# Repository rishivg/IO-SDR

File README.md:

# IO-SDR_Rev_1.1
 
IO-SDR is an open-source software-defined FPGA radio hardware platform that serves as a successor to the Pluto SDR Learning Module. Support includes and is not limited to:

- dual multichannel transmission and reception
- Gigabit Ethernet connection
- Embedded Linux SoC development
- GNU Radio blocks

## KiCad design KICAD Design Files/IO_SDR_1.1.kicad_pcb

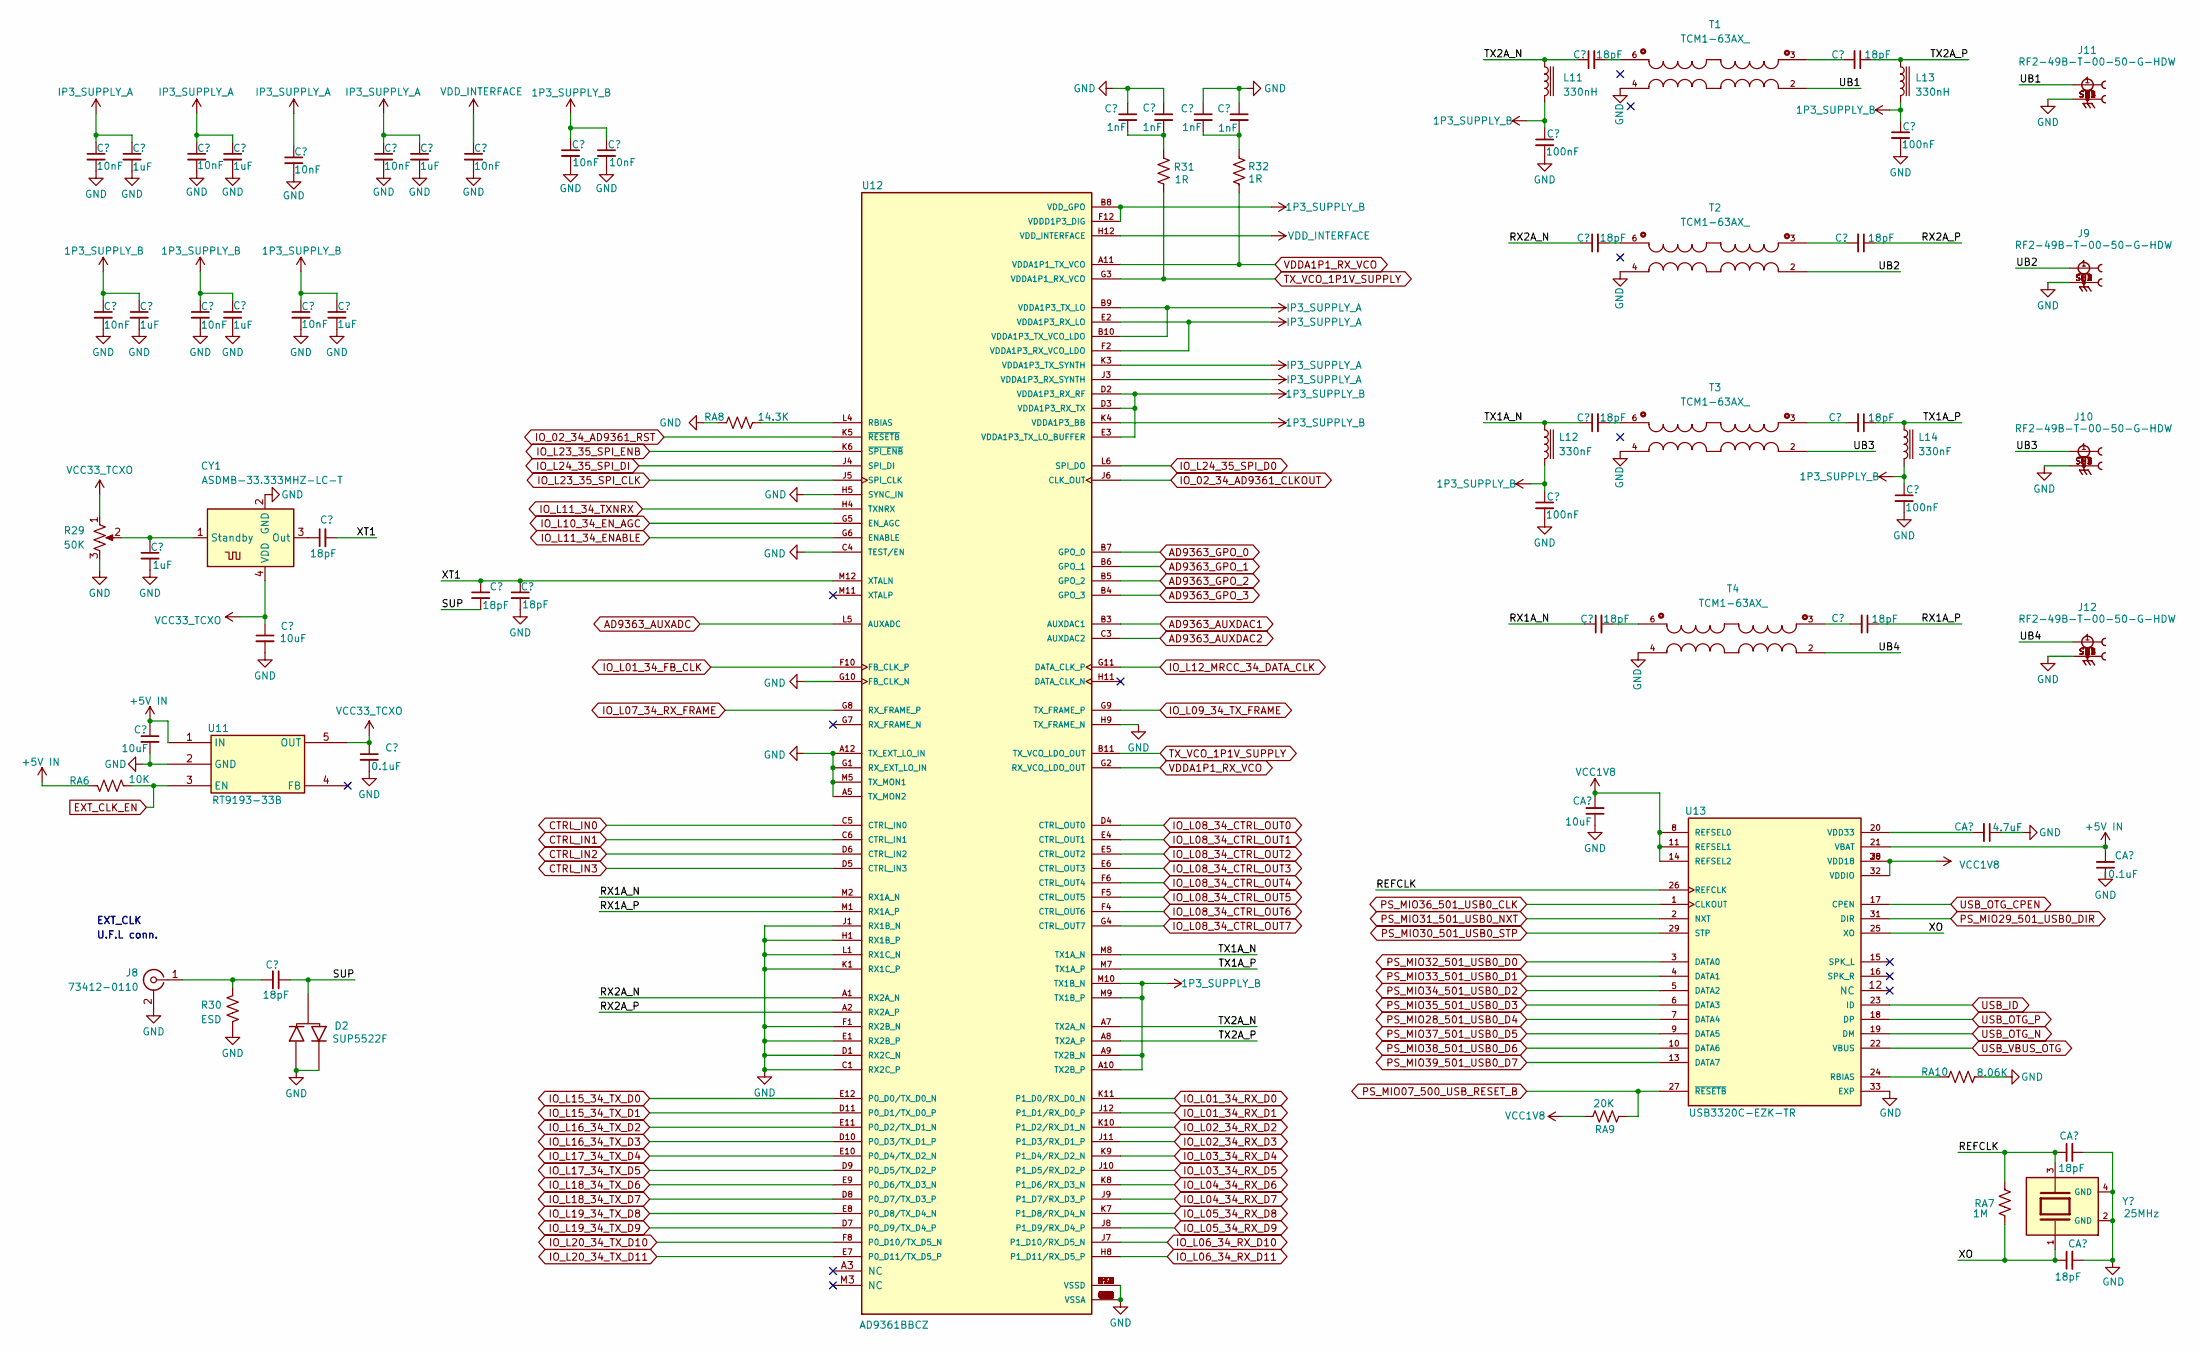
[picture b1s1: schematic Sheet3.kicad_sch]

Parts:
C54, C55, C60, C61, C64, C66, C69, C71, C74, C75: 10nF; C_0402_1005Metric_Pad0.74x0.62mm_HandSolder
C56, C57, C58, C62, C63, C68, C70: 1uF; C_0402_1005Metric_Pad0.74x0.62mm_HandSolder
C59: 10uF; C_0603_1608Metric_Pad1.08x0.95mm_HandSolder
C65, C67, C72, C73, C82, C83, C84, C85, C86, C87, C88, C89: 18pF; C_0402_1005Metric_Pad0.74x0.62mm_HandSolder
C76, C77, C78, C79: 1nF; C_0402_1005Metric_Pad0.74x0.62mm_HandSolder
C80, C81, C90, C91: 100nF; C_0402_1005Metric_Pad0.74x0.62mm_HandSolder
CA5, CA6: 18pF; C_0402_1005Metric_Pad0.74x0.62mm_HandSolder
CA7, CA9: 10uF; C_0603_1608Metric_Pad1.08x0.95mm_HandSolder
CA8, CA11: 0.1uF; C_0402_1005Metric_Pad0.74x0.62mm_HandSolder
CA10: 4.7uF; C_0603_1608Metric_Pad1.08x0.95mm_HandSolder
CY1: ASDMB-33.333MHZ-LC-T; XTAL_ASDMB-33.333MHZ-LC-T
D2: SUP5522F; SOT-23-3
J8: 73412-0110; U.FL_Molex_MCRF_73412-0110_Vertical
J9, J10, J11, J12: RF2-49B-T-00-50-G-HDW; ADAMTECH_RF2-49B-T-00-50-G-HDW; PARTREV 7/20/16
L11, L13: 330nH; L_0402_1005Metric_Pad0.77x0.64mm_HandSolder
L12, L14: 330nF; L_0402_1005Metric_Pad0.77x0.64mm_HandSolder
R29: 50K; Potentiometer_Bourns_3214W_Vertical
R30: ESD; R_0402_1005Metric_Pad0.72x0.64mm_HandSolder
R31, R32: 1R; R_0402_1005Metric_Pad0.72x0.64mm_HandSolder
RA6: 10K; R_0402_1005Metric_Pad0.72x0.64mm_HandSolder
RA7: 1M; R_0402_1005Metric_Pad0.72x0.64mm_HandSolder
RA8: 14.3K; R_0402_1005Metric_Pad0.72x0.64mm_HandSolder
RA9: 20K; R_0402_1005Metric_Pad0.72x0.64mm_HandSolder
RA10: 8.06K; R_0402_1005Metric_Pad0.72x0.64mm_HandSolder
T1, T2, T3, T4: TCM1-63AX_; XFMR_TCM1-63AX_
U11: RT9193-33B
U12: AD9361BBCZ
U13: USB3320C-EZK-TR
Y2: 25MHz; XTAL_TSX-3225_25.0000MF10P-C0; PARTREV N/A

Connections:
+1V2: C55.1, C57.1, C61.1, C63.1, C66.1, C68.1, C74.1, C75.1, C80.1, C81.1, C90.1, C91.1, L11.2, L12.2, L13.2, L14.2, U12.A9 (TX2B_N), U12.A10 (TX2B_P), U12.B8 (VDD_GPO), U12.D2 (VDDA1P3_RX_RF), U12.D3 (VDDA1P3_RX_TX), U12.E3 (VDDA1P3_TX_LO_BUFFER), U12.F12 (VDDD1P3_DIG), U12.K4 (VDDA1P3_BB), U12.M9 (TX1B_P), U12.M10 (TX1B_N); also elsewhere on the board
+1V8: CA9.2, RA9.2, U13.8 (REFSEL0), U13.11 (REFSEL1), U13.14 (REFSEL2), U13.28 (VDD18), U13.30 (VDD18), U13.32 (VDDIO); also elsewhere on the board
+3.3V: CA7.1, CA8.1, CY1.4 (VDD), R29.1, U11.5 (OUT)
+12L: C54.1, C56.1, C60.1, C62.1, C64.1, C69.1, C70.1, U12.B9 (VDDA1P3_TX_LO), U12.B10 (VDDA1P3_TX_VCO_LDO), U12.E2 (VDDA1P3_RX_LO), U12.F2 (VDDA1P3_RX_VCO_LDO), U12.J3 (VDDA1P3_RX_SYNTH), U12.K3 (VDDA1P3_TX_SYNTH); also elsewhere on the board
+VSW: C71.1, U12.H12 (VDD_INTERFACE); also elsewhere on the board
/Sheet3/REFCLK: CA5.1, RA7.1, U13.26 (REFCLK), Y2.3
/Sheet3/RX1A_N: C85.1, U12.M2 (RX1A_N)
/Sheet3/RX1A_P: C89.1, U12.M1 (RX1A_P)
/Sheet3/RX2A_N: C83.1, U12.A1 (RX2A_N)
/Sheet3/RX2A_P: C87.1, U12.A2 (RX2A_P)
/Sheet3/SUP: C65.1, C72.2, D2.3 (D)
/Sheet3/TX1A_N: C84.1, L12.1, U12.M8 (TX1A_N)
/Sheet3/TX1A_P: C88.1, L14.1, U12.M7 (TX1A_P)
/Sheet3/TX2A_N: C82.1, L11.1, U12.A7 (TX2A_N)
/Sheet3/TX2A_P: C86.1, L13.1, U12.A8 (TX2A_P)
/Sheet3/UB1: J11.1, T1.2
/Sheet3/UB2: J9.1, T2.2
/Sheet3/UB3: J10.1, T3.2
/Sheet3/UB4: J12.1, T4.2
/Sheet3/XO: CA6.1, RA7.2, U13.25 (XO), Y2.1
/Sheet3/XT1: C67.2, C72.1, C73.1, U12.M12 (XTALN)
AD9363_AUXADC: U12.L5 (AUXADC)
AD9363_AUXDAC1: U12.B3 (AUXDAC1)
AD9363_AUXDAC2: U12.C3 (AUXDAC2)
AD9363_GPO_0: U12.B7 (GPO_0)
AD9363_GPO_1: U12.B6 (GPO_1)
AD9363_GPO_2: U12.B5 (GPO_2)
AD9363_GPO_3: U12.B4 (GPO_3)
CTRL_IN0: U12.C5 (CTRL_IN0); also elsewhere on the board
CTRL_IN1: U12.C6 (CTRL_IN1); also elsewhere on the board
CTRL_IN2: U12.D6 (CTRL_IN2); also elsewhere on the board
CTRL_IN3: U12.D5 (CTRL_IN3); also elsewhere on the board
EXT_CLK_EN: RA6.2, U11.3 (EN); also elsewhere on the board
GND: C54.2, C55.2, C56.2, C57.2, C58.2, C59.2, C60.2, C61.2, C62.2, C63.2, C64.2, C66.2, C68.2, C69.2, C70.2, C71.2, C73.2, C74.2, C75.2, C76.1, C77.1, C78.1, C79.1, C80.2, C81.2, C90.2, C91.2, CA5.2, CA6.2, CA7.2, CA8.2, CA9.1, CA10.1, CA11.1, CY1.2 (GND), D2.1 (G), D2.2 (S), J8.2 (Ext), J9.SH1, J9.SH2, J9.SH3, J9.SH4, J10.SH1, J10.SH2, J10.SH3, J10.SH4, J11.SH1, J11.SH2, J11.SH3, J11.SH4, J12.SH1, J12.SH2, J12.SH3, J12.SH4, R29.3, R30.2, RA8.2, RA10.2, T1.4, T2.4, T3.4, T4.4, U11.2 (GND), U12.A4 (VSSA), U12.A5 (TX_MON2), U12.A6 (VSSA), U12.A12 (TX_EXT_LO_IN), U12.B1 (VSSA), U12.B2 (VSSA), U12.B12 (VSSA), U12.C1 (RX2C_P), U12.C2 (VSSA), U12.C4 (TEST/EN), U12.C7 (VSSA), U12.C8 (VSSA), U12.C9 (VSSA), U12.C10 (VSSA), U12.C11 (VSSA), U12.C12 (VSSA), U12.D1 (RX2C_N), U12.D12 (VSSD), U12.E1 (RX2B_P), U12.F1 (RX2B_N), U12.F3 (VSSA), U12.F7 (VSSD), U12.F9 (VSSD), U12.F11 (VSSD), U12.G1 (RX_EXT_LO_IN), U12.G10 (FB_CLK_N), U12.G12 (VSSD), U12.H1 (RX1B_P), U12.H2 (VSSA), U12.H3 (VSSA), U12.H5 (SYNC_IN), U12.H6 (VSSA), U12.H7 (VSSD), U12.H9 (TX_FRAME_N), U12.H10 (VSSD), U12.J1 (RX1B_N), U12.J2 (VSSA), U12.K1 (RX1C_P), U12.K2 (VSSA), U12.K12 (VSSD), U12.L1 (RX1C_N), U12.L2 (VSSA), U12.L3 (VSSA), U12.L7 (VSSA), U12.L8 (VSSA), U12.L9 (VSSA), U12.L10 (VSSA), U12.L11 (VSSA), U12.L12 (VSSA), U12.M4 (VSSA), U12.M5 (TX_MON1), U12.M6 (VSSA), U13.33 (EXP), Y2.2 (GND), Y2.4 (GND); also elsewhere on the board
IO_02_34_AD9361_CLKOUT: U12.J6 (CLK_OUT); also elsewhere on the board
IO_02_34_AD9361_RST: U12.K5 (~RESETB); also elsewhere on the board
IO_L01_34_FB_CLK: U12.F10 (FB_CLK_P); also elsewhere on the board
IO_L01_34_RX_D0: U12.K11 (P1_D0/RX_D0_N); also elsewhere on the board
IO_L01_34_RX_D1: U12.J12 (P1_D1/RX_D0_P); also elsewhere on the board
IO_L02_34_RX_D2: U12.K10 (P1_D2/RX_D1_N); also elsewhere on the board
IO_L02_34_RX_D3: U12.J11 (P1_D3/RX_D1_P); also elsewhere on the board
IO_L03_34_RX_D4: U12.K9 (P1_D4/RX_D2_N); also elsewhere on the board
IO_L03_34_RX_D5: U12.J10 (P1_D5/RX_D2_P); also elsewhere on the board
IO_L04_34_RX_D6: U12.K8 (P1_D6/RX_D3_N); also elsewhere on the board
IO_L04_34_RX_D7: U12.J9 (P1_D7/RX_D3_P); also elsewhere on the board
IO_L05_34_RX_D8: U12.K7 (P1_D8/RX_D4_N); also elsewhere on the board
IO_L05_34_RX_D9: U12.J8 (P1_D9/RX_D4_P); also elsewhere on the board
IO_L06_34_RX_D10: U12.J7 (P1_D10/RX_D5_N); also elsewhere on the board
IO_L06_34_RX_D11: U12.H8 (P1_D11/RX_D5_P); also elsewhere on the board
IO_L07_34_RX_FRAME: U12.G8 (RX_FRAME_P); also elsewhere on the board
IO_L08_34_CTRL_OUT0: U12.D4 (CTRL_OUT0); also elsewhere on the board
IO_L08_34_CTRL_OUT1: U12.E4 (CTRL_OUT1); also elsewhere on the board
IO_L08_34_CTRL_OUT2: U12.E5 (CTRL_OUT2)
IO_L08_34_CTRL_OUT3: U12.E6 (CTRL_OUT3)
IO_L08_34_CTRL_OUT4: U12.F6 (CTRL_OUT4)
IO_L08_34_CTRL_OUT5: U12.F5 (CTRL_OUT5)
IO_L08_34_CTRL_OUT6: U12.F4 (CTRL_OUT6)
IO_L08_34_CTRL_OUT7: U12.G4 (CTRL_OUT7)
IO_L09_34_TX_FRAME: U12.G9 (TX_FRAME_P); also elsewhere on the board
IO_L10_34_EN_AGC: U12.G5 (EN_AGC); also elsewhere on the board
IO_L11_34_ENABLE: U12.G6 (ENABLE); also elsewhere on the board
IO_L11_34_TXNRX: U12.H4 (TXNRX); also elsewhere on the board
IO_L12_MRCC_34_DATA_CLK: U12.G11 (DATA_CLK_P); also elsewhere on the board
IO_L15_34_TX_D0: U12.E12 (P0_D0/TX_D0_N); also elsewhere on the board
IO_L15_34_TX_D1: U12.D11 (P0_D1/TX_D0_P); also elsewhere on the board
IO_L16_34_TX_D2: U12.E11 (P0_D2/TX_D1_N); also elsewhere on the board
IO_L16_34_TX_D3: U12.D10 (P0_D3/TX_D1_P); also elsewhere on the board
IO_L17_34_TX_D4: U12.E10 (P0_D4/TX_D2_N); also elsewhere on the board
IO_L17_34_TX_D5: U12.D9 (P0_D5/TX_D2_P); also elsewhere on the board
IO_L18_34_TX_D6: U12.E9 (P0_D6/TX_D3_N); also elsewhere on the board
IO_L18_34_TX_D7: U12.D8 (P0_D7/TX_D3_P); also elsewhere on the board
IO_L19_34_TX_D8: U12.E8 (P0_D8/TX_D4_N); also elsewhere on the board
IO_L19_34_TX_D9: U12.D7 (P0_D9/TX_D4_P); also elsewhere on the board
IO_L20_34_TX_D10: U12.F8 (P0_D10/TX_D5_N); also elsewhere on the board
IO_L20_34_TX_D11: U12.E7 (P0_D11/TX_D5_P); also elsewhere on the board
IO_L23_35_SPI_CLK: U12.J5 (SPI_CLK); also elsewhere on the board
IO_L23_35_SPI_ENB: U12.K6 (~SPI_ENB); also elsewhere on the board
IO_L24_35_SPI_D0: U12.L6 (SPI_DO); also elsewhere on the board
IO_L24_35_SPI_DI: U12.J4 (SPI_DI); also elsewhere on the board
unnamed: C76.2, C77.2, R31.1
unnamed: C78.2, C79.2, R32.1
unnamed: C82.2, T1.6
unnamed: C83.2, T2.6
unnamed: C84.2, T3.6
unnamed: C85.2, T4.6
unnamed: C86.2, T1.3
unnamed: C87.2, T2.3
unnamed: C88.2, T3.3
unnamed: C89.2, T4.3
unnamed: C67.1, CY1.3 (Out)
unnamed: C58.1, CY1.1 (Standby), R29.2
unnamed: C65.2, J8.1 (In), R30.1
unnamed: RA8.1, U12.L4 (RBIAS)
unnamed: RA10.1, U13.24 (RBIAS)
unnamed: CA10.2, U13.20 (VDD33)
PS_MIO07_500_USB_RESET_B: RA9.1, U13.27 (~RESETB); also elsewhere on the board
PS_MIO28_501_USB0_D4: U13.7 (DATA4); also elsewhere on the board
PS_MIO29_501_USB0_DIR: U13.31 (DIR); also elsewhere on the board
PS_MIO30_501_USB0_STP: U13.29 (STP); also elsewhere on the board
PS_MIO31_501_USB0_NXT: U13.2 (NXT); also elsewhere on the board
PS_MIO32_501_USB0_D0: U13.3 (DATA0); also elsewhere on the board
PS_MIO33_501_USB0_D1: U13.4 (DATA1); also elsewhere on the board
PS_MIO34_501_USB0_D2: U13.5 (DATA2); also elsewhere on the board
PS_MIO35_501_USB0_D3: U13.6 (DATA3); also elsewhere on the board
PS_MIO36_501_USB0_CLK: U13.1 (CLKOUT); also elsewhere on the board
PS_MIO37_501_USB0_D5: U13.9 (DATA5); also elsewhere on the board
PS_MIO38_501_USB0_D6: U13.10 (DATA6); also elsewhere on the board
PS_MIO39_501_USB0_D7: U13.13 (DATA7); also elsewhere on the board
TX_VCO_1P1V_SUPPLY: R31.2, U12.B11 (TX_VCO_LDO_OUT), U12.G3 (VDDA1P1_RX_VCO)
USB_ID: U13.23 (ID); also elsewhere on the board
USB_OTG_CPEN: U13.17 (CPEN); also elsewhere on the board
USB_OTG_N: U13.19 (DM); also elsewhere on the board
USB_OTG_P: U13.18 (DP); also elsewhere on the board
USB_VBUS_OTG: U13.22 (VBUS); also elsewhere on the board
VDDA1P1_RX_VCO: R32.2, U12.A11 (VDDA1P1_TX_VCO), U12.G2 (RX_VCO_LDO_OUT)

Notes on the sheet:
EXT_CLK
U.F.L conn.
